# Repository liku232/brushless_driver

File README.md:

# 3 Phasen Inverter
Verpflichtendes TGM-Sommerprojekt
- [Lastenheft](Lastenheft.md)
- [Linkliste](linklist.md)

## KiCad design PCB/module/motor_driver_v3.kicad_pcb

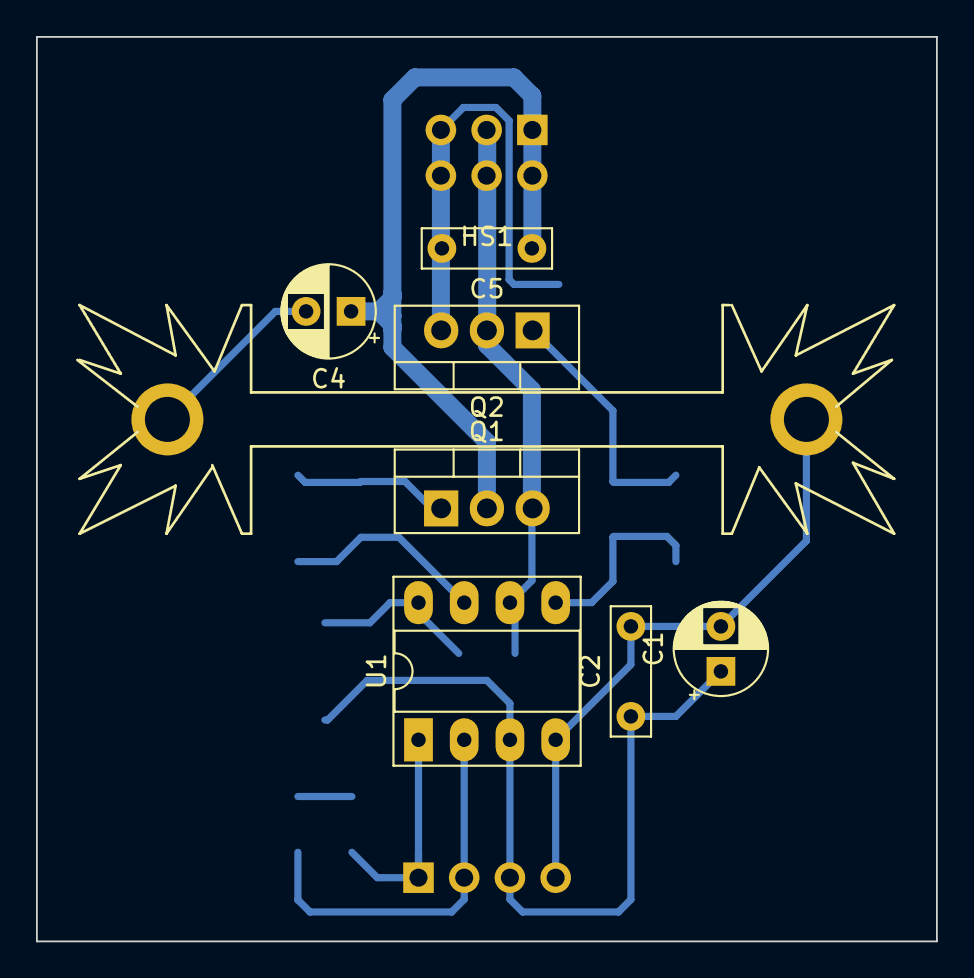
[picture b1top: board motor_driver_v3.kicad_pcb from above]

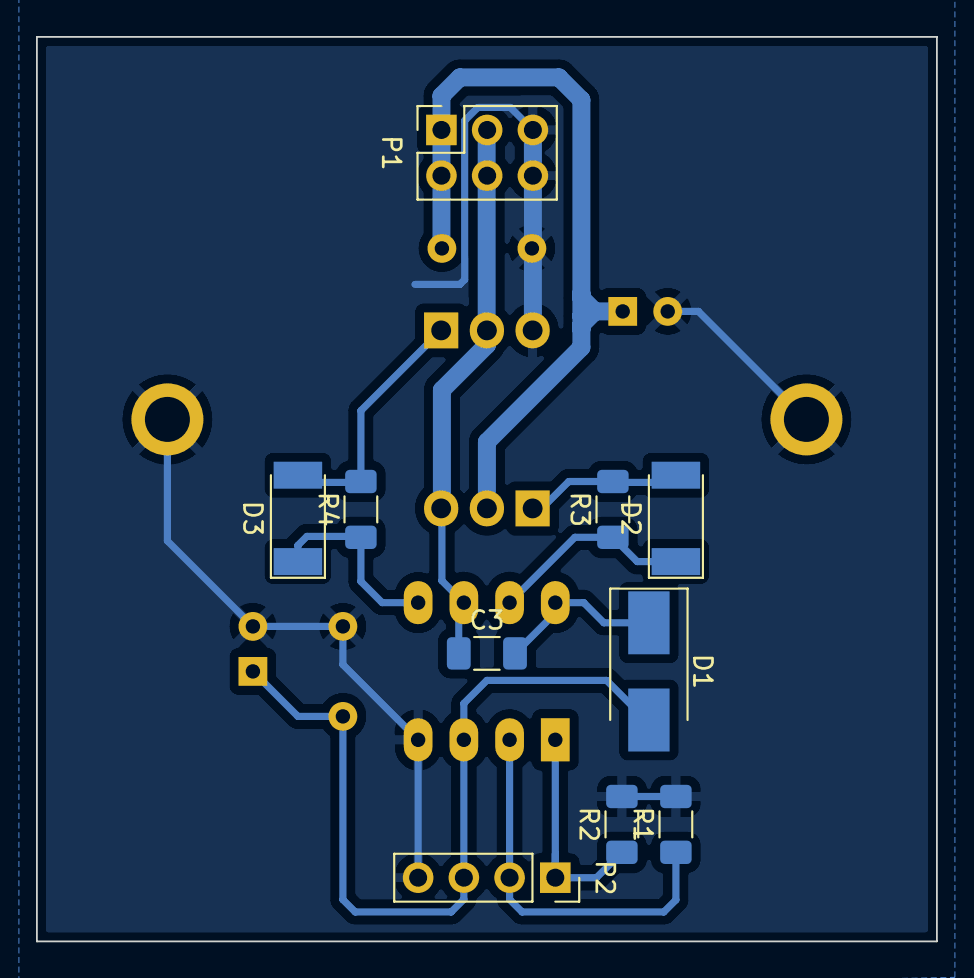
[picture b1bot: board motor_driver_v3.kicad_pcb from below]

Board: 2 copper layers, 50.0 x 50.2 mm, 18 parts (10 on the bottom side), 11 nets.

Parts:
C1, C4: CP1; CP_Radial_D5.0mm_P2.50mm
C2, C5: C; C_Rect_L7.0mm_W2.0mm_P5.00mm
C3: C; C_1206_3216Metric_Pad1.33x1.80mm_HandSolder
D1: D_Schottky; D_SMB_Handsoldering
D2, D3: D_Schottky; D_MELF
HS1: Heatsink_Pad; Heatsink_Fischer_SK409_2xDrill2.3mm_soldered
P1: CONN_3X2; PinSocket_2x03_P2.54mm_Vertical
P2: CONN_4; PinSocket_1x04_P2.54mm_Vertical
Q1, Q2: IRF540N; TO-220-3_Vertical
R1, R2, R3, R4: R; R_1206_3216Metric_Pad1.30x1.75mm_HandSolder
U1: L6387E; DIP-8_W7.62mm_Socket_LongPads

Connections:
+24V: C4.1, C5.1, P1.1, P1.2, Q1.2 (D)
/Vghs1: D2.1 (K), R3.1, U1.7 (HVG)
/Vgls1: D3.1 (K), R4.1, U1.5 (LVG)
/hin1: P2.2, R1.1, U1.2 (HIN)
/lin1: P2.1, R2.1, U1.1 (LIN)
/out: C3.1, P1.3, P1.4, Q1.3 (S), Q2.2 (D), U1.6 (OUT)
GND: C1.2, C2.2, C4.2, C5.2, HS1.1, P1.5, P1.6, P2.4, Q2.3 (S), R1.2, R2.2, U1.4 (GND)
unnamed: C3.2, D1.1 (K), U1.8 (Vboot)
unnamed: D2.2 (A), Q1.1 (G), R3.2
unnamed: D3.2 (A), Q2.1 (G), R4.2
VCC: C1.1, C2.1, D1.2 (A), P2.3, U1.3 (Vcc)

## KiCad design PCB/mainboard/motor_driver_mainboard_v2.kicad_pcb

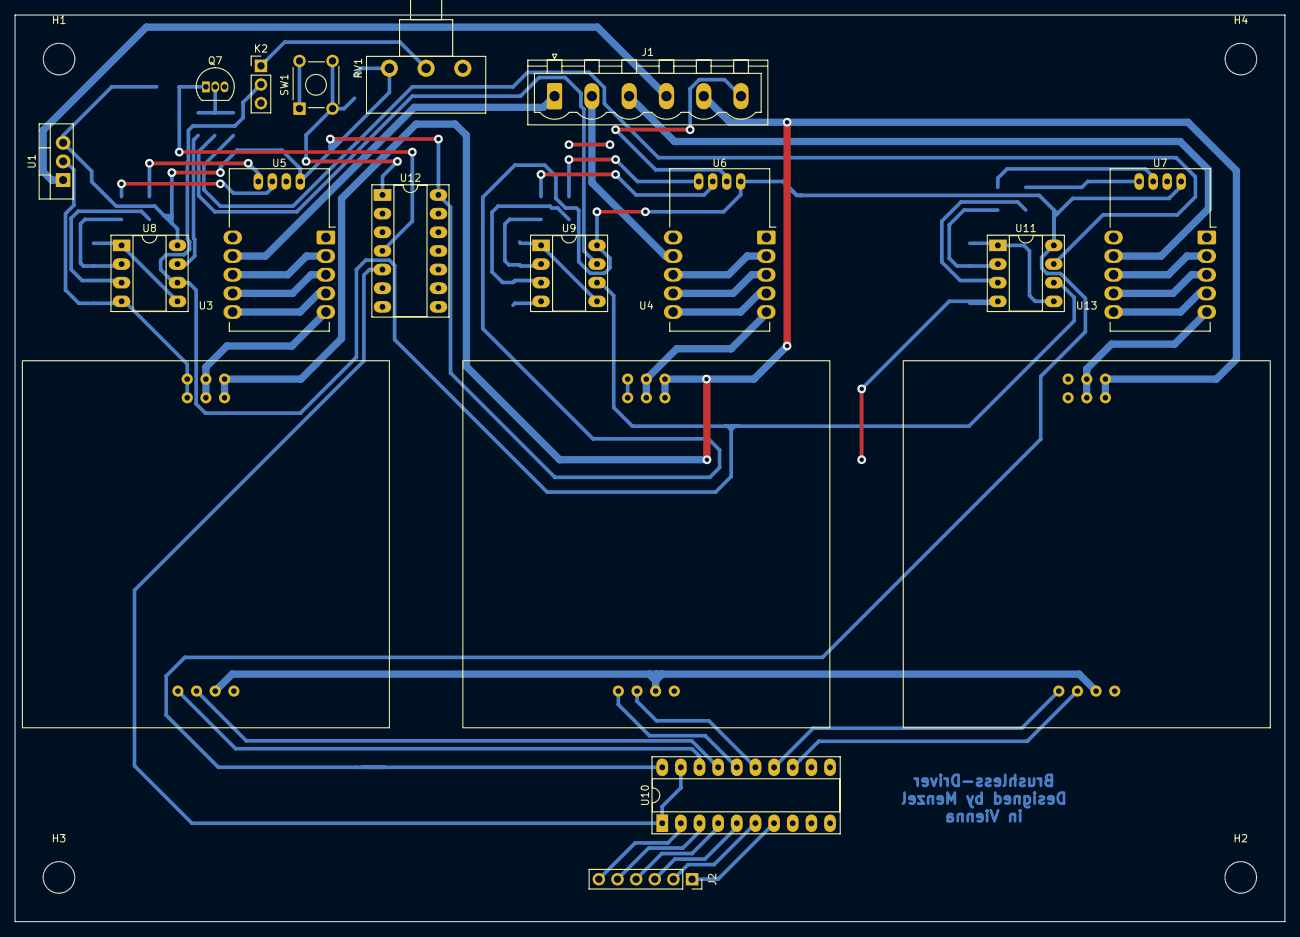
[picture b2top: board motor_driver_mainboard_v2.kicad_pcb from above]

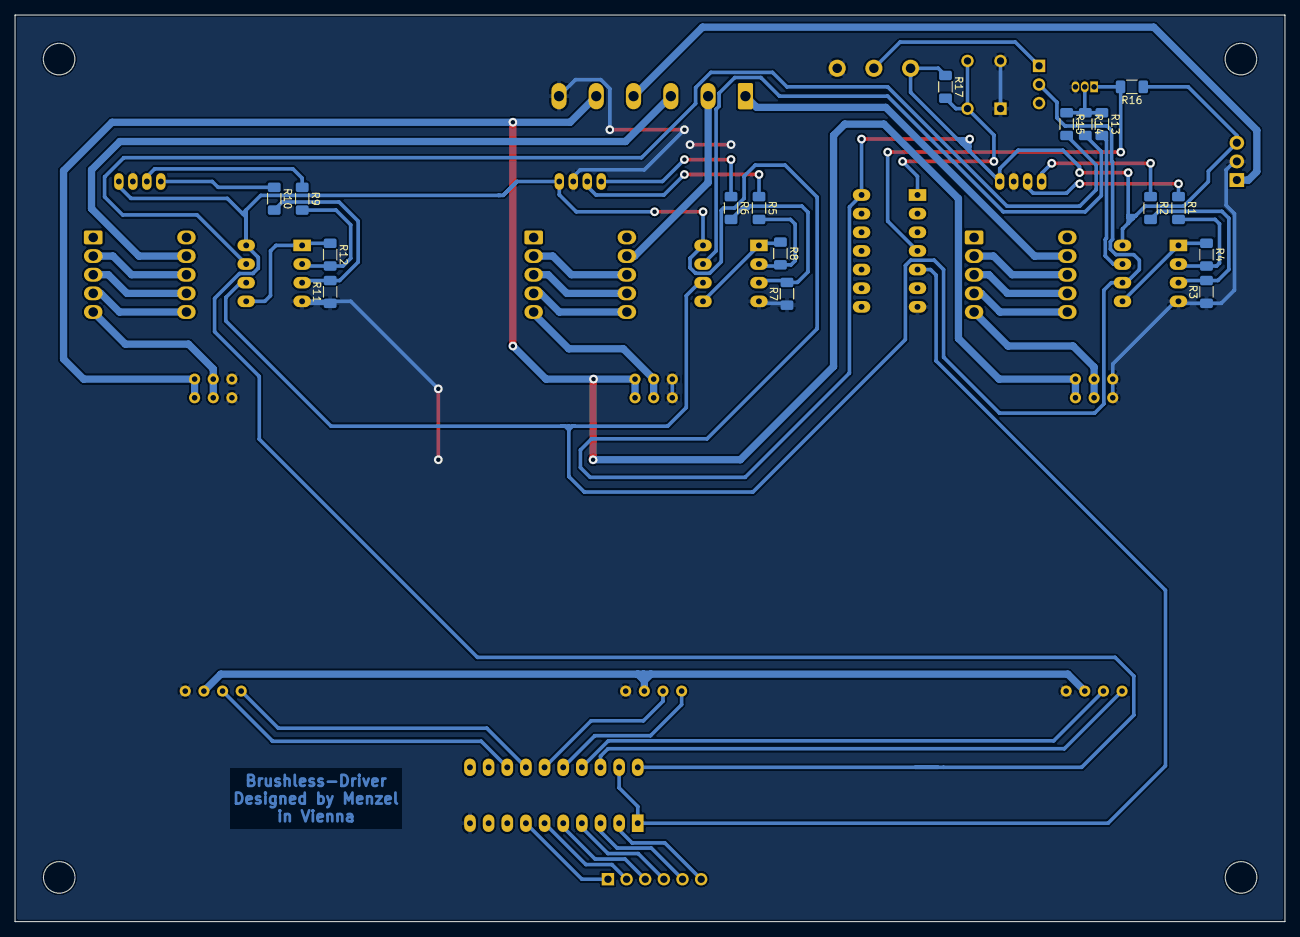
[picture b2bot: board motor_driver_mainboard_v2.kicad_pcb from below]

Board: 2 copper layers, 173.0 x 123.5 mm, 39 parts (17 on the bottom side), 55 nets.

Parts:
H1, H2, H3, H4: MountingHole; MountingHole_4.3mm_M4
J1: Conn_01x06; PhoenixContact_MSTBVA_2,5_6-G-5,08_1x06_P5.08mm_Vertical
J2: Conn_01x06; PinSocket_1x06_P2.54mm_Vertical
K2: CONN_3; PinHeader_1x03_P2.54mm_Vertical
Q7: BC547; TO-92_Inline
R1, R2, R3, R4, R5, R6, R7, R8, R9, R10, R11, R12, R13, R14, R15, R16, R17: R_Small; R_1206_3216Metric_Pad1.30x1.75mm_HandSolder
RV1: POT; Potentiometer_Piher_T-16H_Single_Horizontal
SW1: SW_Push_Dual; SW_TH_Tactile_Omron_B3F-10xx
U1: L7805; TO-220-3_Vertical
U3, U4, U13: Half_Bridge; half_bridge
U5, U6, U7: CKSR_25-NP; LEM_CKSR
U8, U9, U11: LM358; DIP-8_W7.62mm_Socket_LongPads
U10: 74LS541; DIP-20_W7.62mm_Socket_LongPads
U12: 74HC74; DIP-14_W7.62mm_Socket_LongPads

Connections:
+5V: R16.1, R17.1, RV1.3, U1.3 (OUT), U5.14 (Uc), U6.14 (Uc), U7.14 (Uc), U8.8 (V+), U9.8 (V+), U10.20 (VCC), U11.8 (V+), U12.14 (VCC)
+15V: J1.5, U3.3 (Vp), U4.3 (Vp), U13.3 (Vp)
/PA7: J2.5, U10.3 (A1)
/PA8: J2.6, U10.2 (A0)
/PA9: J2.4, U10.4 (A2)
/PA10: J2.2, U10.6 (A4)
/PB0: J2.3, U10.5 (A3)
/PB1: J2.1, U10.7 (A5)
/U: J1.1, U5.9 (OUT)
/V: J1.2, U6.9 (OUT)
/V_iu: R4.1, U8.1, U8.5 (+)
/V_iv: R8.1, U9.1, U9.5 (+)
/V_iw: R12.1, U11.1, U11.5 (+)
/V_of: Q7.2 (B), R13.1, R14.1, R15.1
/V_ofu: R13.2, U8.7
/V_ofv: R14.2, U9.7
/V_ofw: R15.2, U11.7
/Vgate: U10.1 (G1), U10.19 (G2), U12.5 (Q)
/Vith: K2.2 (PM), U8.6 (-), U9.6 (-), U11.6 (-)
/Vout_U: R1.1, U5.12 (Vout)
/Vout_V: R5.1, U6.12 (Vout)
/Vout_W: R9.1, U7.12 (Vout)
/Vref_U: R2.1, U5.11 (Vref)
/Vref_V: R6.1, U6.11 (Vref)
/Vref_W: R10.1, U7.11 (Vref)
/W: J1.3, U7.9 (OUT)
/coil1: U5.4 (IN), U5.6 (OUT)
/coil2: U5.3 (IN), U5.7 (OUT)
/coil3: U5.2 (IN), U5.8 (OUT)
/coil4: U6.4 (IN), U6.6 (OUT)
/coil5: U6.3 (IN), U6.7 (OUT)
/coil6: U6.2 (IN), U6.8 (OUT)
/coil7: U7.4 (IN), U7.6 (OUT)
/coil8: U7.3 (IN), U7.7 (OUT)
/coil9: U7.2 (IN), U7.8 (OUT)
/hin_u: U3.5 (hin), U10.17 (Y1)
/hin_v: U4.5 (hin), U10.15 (Y3)
/hin_w: U10.13 (Y5), U13.5 (hin)
/lin_u: U3.4 (lin), U10.18 (Y0)
/lin_v: U4.4 (lin), U10.16 (Y2)
/lin_w: U10.14 (Y4), U13.4 (lin)
/out1: U3.2 (out), U5.5 (IN)
/out2: U4.2 (out), U6.5 (IN)
/out3: U7.5 (IN), U13.2 (out)
/reset: R17.2, SW1.2, U12.1 (~R)
GND: J1.6, Q7.3 (E), R3.1, R7.1, R11.1, RV1.1, SW1.1, U1.2 (GND), U3.1 (GND), U4.1 (GND), U5.13 (GND), U6.13 (GND), U7.13 (GND), U8.4 (V-), U9.4 (V-), U10.10 (GND), U11.4 (V-), U12.7 (GND), U13.1 (GND)
unnamed: K2.1, RV1.2
unnamed: Q7.1 (C), R16.2, U12.4 (~S)
unnamed: R1.2, R4.2, U8.2 (-)
unnamed: R2.2, R3.2, U8.3 (+)
unnamed: R5.2, R8.2, U9.2 (-)
unnamed: R6.2, R7.2, U9.3 (+)
unnamed: R10.2, R11.2, U11.3 (+)
unnamed: R9.2, R12.2, U11.2 (-)
VCC: J1.4, U1.1 (IN)

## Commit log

2022-01-27 Create linklist
2022-01-27 Rename linklist to linklist.md
2022-01-27 name change
2022-02-17 changed Lastenheft
2022-06-23 Create test
2022-06-23 Create mainboard
